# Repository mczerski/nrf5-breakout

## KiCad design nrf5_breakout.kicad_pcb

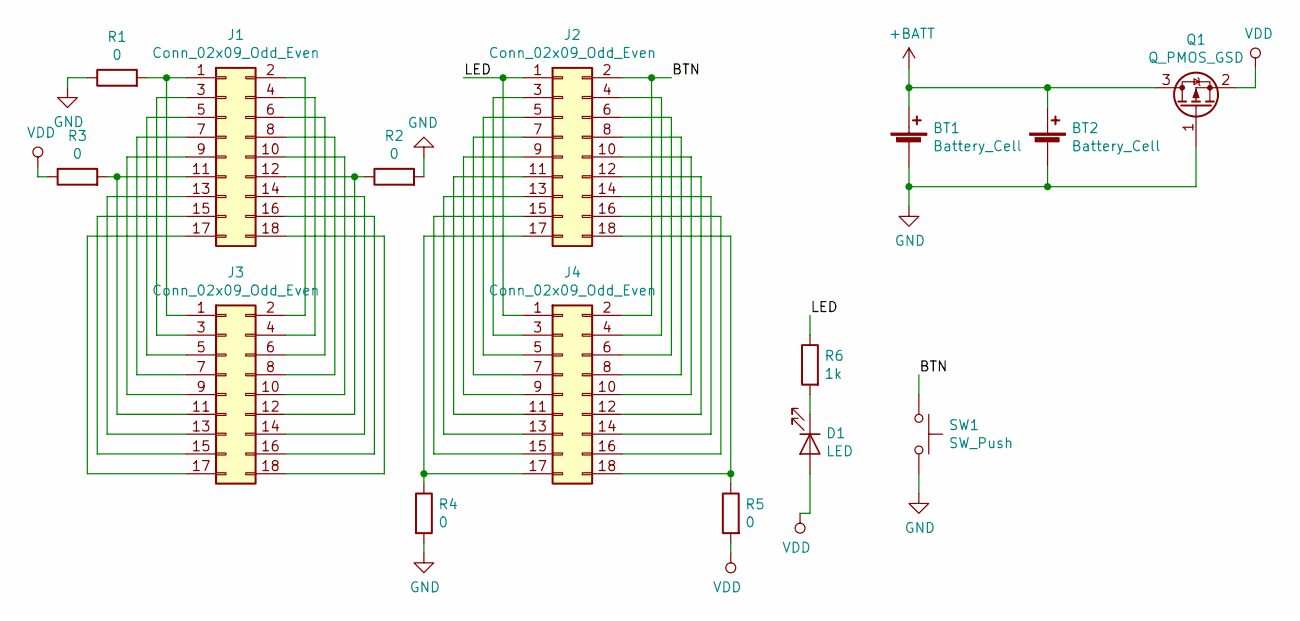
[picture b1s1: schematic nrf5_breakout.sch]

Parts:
BT1: Battery_Cell; BatteryHolder_Keystone_1060_1x2032
BT2: Battery_Cell; CR123_holder
D1: LED; LED_0805_2012Metric
J1, J2: Conn_02x09_Odd_Even; PinHeader_2x09_P2.00mm_Vertical
J3, J4: Conn_02x09_Odd_Even; PinHeader_2x09_P2.54mm_Vertical
Q1: Q_PMOS_GSD; SOT-23
R1, R2, R3, R4, R5: 0; R_0603_1608Metric
R6: 1k; R_0603_1608Metric
SW1: SW_Push; SW_SPST_EVQPE1

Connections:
+BATT: BT1.1 (+), BT2.1 (+), Q1.3 (D)
/BTN: J2.2, J4.2, SW1.1
/LED: J2.1, J4.1, R6.1
GND: BT1.2 (-), BT2.2 (-), Q1.1 (G), R1.1, R2.2, R4.2, SW1.2
unnamed: D1.1 (K), R6.2
unnamed: J1.1, J3.1, R1.2
unnamed: J1.2, J3.2
unnamed: J1.3, J3.3
unnamed: J1.4, J3.4
unnamed: J1.5, J3.5
unnamed: J1.6, J3.6
unnamed: J1.7, J3.7
unnamed: J1.8, J3.8
unnamed: J1.9, J3.9
unnamed: J1.10, J3.10
unnamed: J1.11, J3.11, R3.2
unnamed: J1.12, J3.12, R2.1
unnamed: J1.13, J3.13
unnamed: J1.14, J3.14
unnamed: J1.15, J3.15
unnamed: J1.16, J3.16
unnamed: J1.17, J3.17
unnamed: J1.18, J3.18
unnamed: J2.3, J4.3
unnamed: J2.4, J4.4
unnamed: J2.5, J4.5
unnamed: J2.6, J4.6
unnamed: J2.7, J4.7
unnamed: J2.8, J4.8
unnamed: J2.9, J4.9
unnamed: J2.10, J4.10
unnamed: J2.11, J4.11
unnamed: J2.12, J4.12
unnamed: J2.13, J4.13
unnamed: J2.14, J4.14
unnamed: J2.15, J4.15
unnamed: J2.16, J4.16
unnamed: J2.17, J4.17, R4.1
unnamed: J2.18, J4.18, R5.1
VDD: D1.2 (A), Q1.2 (S), R3.1, R5.2

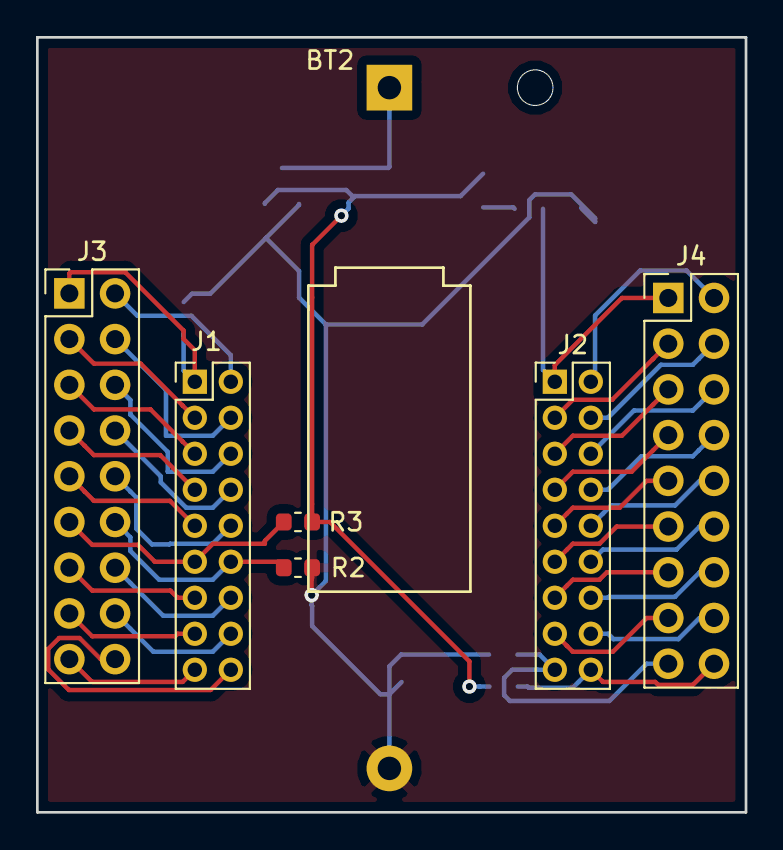
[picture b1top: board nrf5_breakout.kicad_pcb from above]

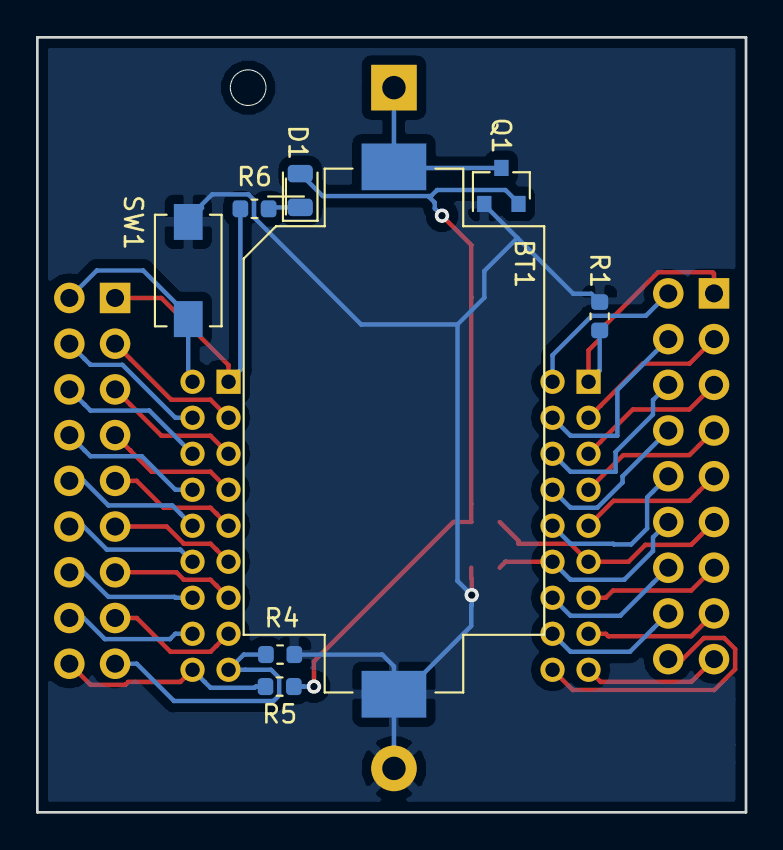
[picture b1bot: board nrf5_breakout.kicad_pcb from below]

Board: 2 copper layers, 39.4 x 43.1 mm, 15 parts (8 on the bottom side), 40 nets.
